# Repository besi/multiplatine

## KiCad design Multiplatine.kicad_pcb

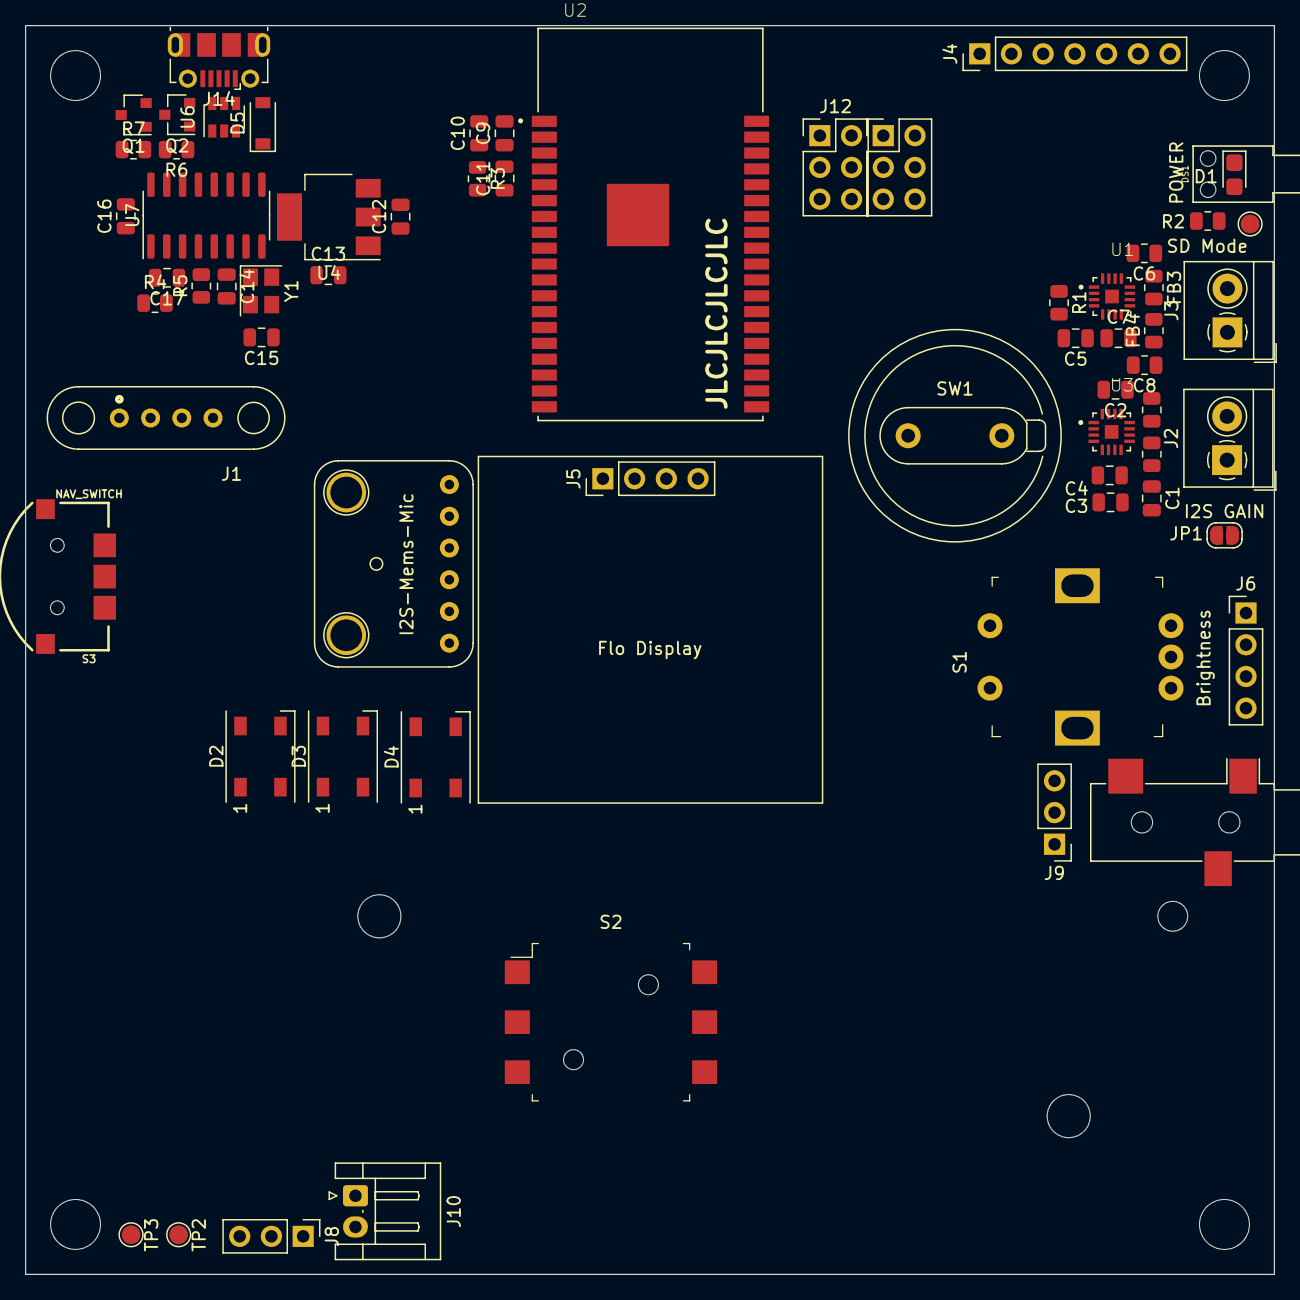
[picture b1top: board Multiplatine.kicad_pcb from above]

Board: 2 copper layers, 100.0 x 100.0 mm, 66 parts (1 on the bottom side), 51 nets, no tracks yet.

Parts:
BT1: Battery_Cell; BatteryHolder_Keystone_1042_1x18650
C1, C2: C_Small; C_0805_2012Metric
C3, C5, C9, C10, C12, C13: 10uF; C_0805_2012Metric
C4, C7: 0.1uF; C_0805_2012Metric
C6, C8: C_Small; R_0805_2012Metric
C11: 1uF; C_0805_2012Metric
C14, C15, C16, C17: 22pF; C_0805_2012Metric
D1: POWER; LED_0805_2012Metric_Castellated
D2, D3, D4: WS2812B; LED_WS2812B_PLCC4_5.0x5.0mm_P3.2mm
D5: D_Schottky; D_SOD-123
DS1: SLP3-200-100-F; BIVAR_SLP3-200-100-F
FB1, FB2, FB3, FB4: Ferrite_Bead_Small; R_0805_2012Metric
J1: Pogo Pins (QWIIC); MagneticPogoPinFlat4
J2: AUDIO Left; TerminalBlock_4Ucon_1x02_P3.50mm_Horizontal
J3: AUDIO Right; TerminalBlock_4Ucon_1x02_P3.50mm_Horizontal
J4: SD Card; PinHeader_1x07_P2.54mm_Vertical
J5: Flo Display; PinHeader_1x04_P2.54mm_Vertical
J6: Brightness; PinHeader_1x04_P2.54mm_Vertical
J7: 1 Wire; Jack_3.5mm_CUI_SJ-3523-SMT_Horizontal
J8: 1Wire Tester; PinHeader_1x03_P2.54mm_Vertical
J9: POWER; PinHeader_1x03_P2.54mm_Vertical
J10: Conn_01x02_Male; JST_EH_S2B-EH_1x02_P2.50mm_Horizontal
J12, J13: Conn_02x03_Odd_Even; PinHeader_2x03_P2.54mm_Vertical
J14: USB_B_Micro; USB_Micro-B_Molex-105017-0001
JP1: I2S GAIN; SolderJumper-2_P1.3mm_Open_RoundedPad1.0x1.5mm
Q1, Q2: S8050; SOT-23
R1: 210k; R_0805_2012Metric
R2: 1k; R_0805_2012Metric
R3, R6, R7: 10k; R_0805_2012Metric
R4, R5: 470; R_0805_2012Metric
S1: PEC11R-4215F-S0024; Rotary_Encoder_Switched_PEC11R
S2: JS5208; Switch_Nav_12.4x12.4mm_SMD_JS5208
S3: NAV_SWITCH
SW1: SW_Push; Switch1104_Schurter
TP1: SD Mode; TestPoint_Pad_D1.5mm
TP2: BAT+; TestPoint_Pad_D1.5mm
TP3: BAT-; TestPoint_Pad_D1.5mm
U1, U3: MAX98357AETE+T; QFN50P300X300X80-17N
U2: ESP32-WROVER; XCVR_ESP32-WROVER-B_(16MB)
U4: AMS1117-3.3; SOT-223-3_TabPin2
U5: I2S-Mems-Mic; Adafruit-MEMS-Mic
U6: USBLC6-2SC6; SOT-23-6
U7: CH340G; SOIC-16_3.9x9.9mm_P1.27mm
Y1: 12 MHZ; Crystal_SMD_3225-4Pin_3.2x2.5mm

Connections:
1WIRE: J7.T, J8.2, U2.26
+3V3: C3.1, C4.1, C5.1, C7.1, C9.1, C10.1, C13.1, C16.2, C17.1, D1.2, D2.1, D3.1, D4.1, J1.2, J5.2, J6.1, J9.2, J13.4, R1.2, R3.2, U1.7, U1.8, U2.2, U3.4, U3.7, U3.8, U4.2, U5.1, U7.4, U7.16
+5V: C12.2, D5.1, J4.1, U4.3
+BATT: BT1.1, J10.2, TP2.1
-BATT: BT1.2, J10.1, TP3.1
BRIGHTNESS_ANALOG: J6.4, U2.11
BRIGHTNESS_DIGITAL: J6.3, U2.10
EN: C11.2, Q1.3, R3.1, U2.3
GND: C1.2, C2.2, C3.2, C4.2, C5.2, C6.2, C7.2, C8.2, C9.2, C10.2, C11.1, C12.1, C13.2, C14.2, C15.2, C16.1, C17.2, D2.3, D3.3, D4.3, J1.1, J4.7, J5.1, J6.2, J7.R, J7.S, J8.1, J8.3, J9.1, J12.3, J13.2, J14.4, J14.5, J14.6, JP1.2, R2.2, S1.2, S1.3, S1.C, U1.3, U1.11, U1.15, U2.1, U2.15, U2.38, U2.39, U3.3, U3.11, U3.15, U4.1, U5.2, U5.6, U6.2, U7.1, Y1.2
I2C_SCL: J1.4, J5.3, U2.19
I2C_SDA: J1.3, J5.4, U2.18
I2S_BCK: J12.5, U1.16, U2.33, U3.16, U5.3
I2S_DATA_IN: J13.6, U2.6, U5.4
I2S_DATA_OUT: U1.1, U2.12, U3.1
I2S_LRCLK: J12.1, U1.14, U2.36, U3.14, U5.5
I2S_OUTPUT_GAIN: JP1.1, U1.2, U3.2
NEOPIXEL: D2.4, U2.14
unnamed: C1.1, FB2.1, J2.2
unnamed: C2.1, FB1.1, J2.1
unnamed: C6.1, FB4.1, J3.2
unnamed: C8.1, FB3.1, J3.1
unnamed: C14.1, U7.7, Y1.1
unnamed: C15.1, U7.8, Y1.3
unnamed: D1.1, R2.1
unnamed: D2.2, D3.4
unnamed: D3.2, D4.4
unnamed: FB1.2, U3.10
unnamed: FB2.2, U3.9
unnamed: FB3.2, U1.10
unnamed: FB4.2, U1.9
unnamed: Q1.1, R7.2, U7.14
unnamed: Q1.2, R6.1
unnamed: Q2.1, R6.2, U7.13
unnamed: Q2.2, R7.1
unnamed: R1.1, TP1.1, U1.4
unnamed: R4.2, U7.2
unnamed: R5.2, U7.3
ROTARY_A: S1.A, U2.8
ROTARY_B: S1.B, U2.9
ROTARY_SWITCH: S1.1, U2.7
RX: R4.1, U2.34
SPI_CS: J4.3, U2.29
SPI_MISO: J4.6, U2.31
SPI_MOSI: J4.4, U2.37
SPI_SCK: J4.5, U2.30
TX: R5.1, U2.35
USB_CONN_D+: J14.3, U6.6
USB_CONN_D-: J14.2, U6.4
USB_D+: U6.1, U7.5
USB_D-: U6.3, U7.6
VUSB: D5.2, J14.1, U6.5
